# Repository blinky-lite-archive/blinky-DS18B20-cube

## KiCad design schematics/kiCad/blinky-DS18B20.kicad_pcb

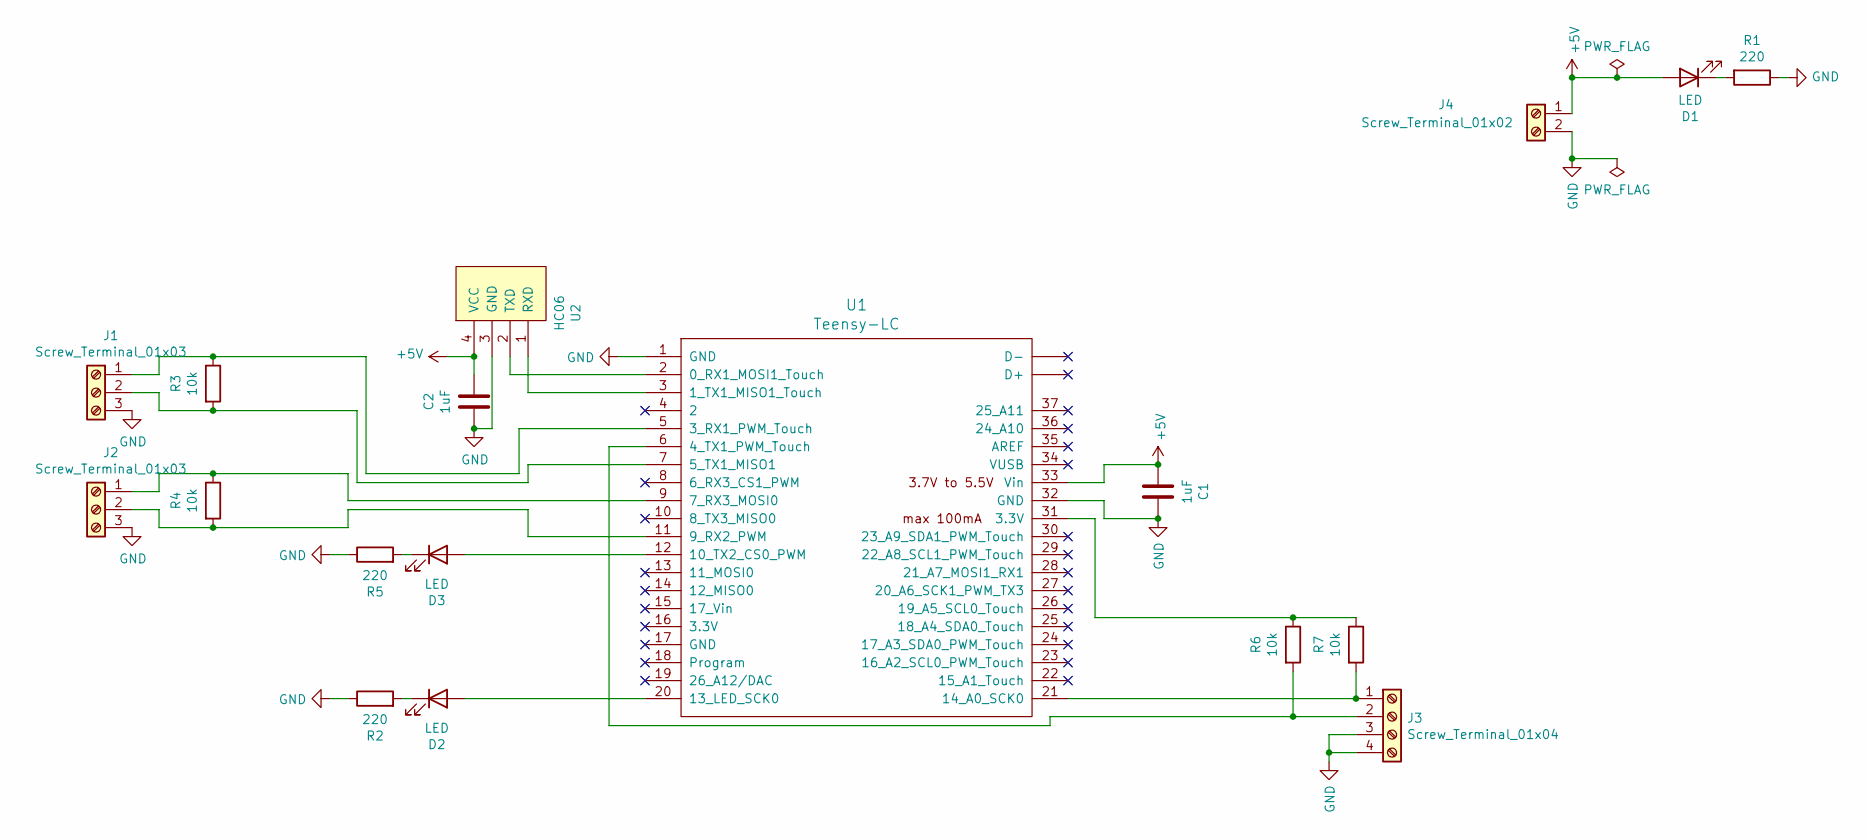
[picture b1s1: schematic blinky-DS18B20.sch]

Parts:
C1, C2: 1uF; C_1206_3216Metric_Pad1.33x1.80mm_HandSolder
D1, D2, D3: LED; LED_D5.0mm
J1, J2: Screw_Terminal_01x03; TerminalBlock_bornier-3_P5.08mm
J3: Screw_Terminal_01x04; TerminalBlock_bornier-4_P5.08mm
J4: Screw_Terminal_01x02; TerminalBlock_bornier-2_P5.08mm
R1, R2, R5: 220; R_1206_3216Metric_Pad1.30x1.75mm_HandSolder
R3, R4, R6, R7: 10k; R_1206_3216Metric_Pad1.30x1.75mm_HandSolder
U1: Teensy-LC; Teensy30_31_32_LC
U2: HC06

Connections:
+5V: C1.2, C2.1, D1.2 (A), J4.1, U1.33 (Vin), U2.4 (VCC)
GND: C1.1, C2.2, J1.3, J2.3, J3.3, J3.4, J4.2, R1.1, R2.1, R5.1, U1.1 (GND), U1.32 (GND), U2.3 (GND)
unnamed: D1.1 (K), R1.2
unnamed: D2.1 (K), R2.2
unnamed: D2.2 (A), U1.20 (13_LED_SCK0)
unnamed: D3.1 (K), R5.2
unnamed: D3.2 (A), U1.12 (10_TX2_CS0_PWM)
unnamed: J1.1, R3.1, U1.5 (3_RX1_PWM_Touch)
unnamed: J1.2, R3.2, U1.7 (5_TX1_MISO1)
unnamed: J2.1, R4.1, U1.9 (7_RX3_MOSI0)
unnamed: J2.2, R4.2, U1.11 (9_RX2_PWM)
unnamed: J3.1, R7.2, U1.21 (14_A0_SCK0)
unnamed: J3.2, R6.2, U1.6 (4_TX1_PWM_Touch)
unnamed: R6.1, R7.1, U1.31 (3.3V)
unnamed: U1.2 (0_RX1_MOSI1_Touch), U2.2 (TXD)
unnamed: U1.3 (1_TX1_MISO1_Touch), U2.1 (RXD)

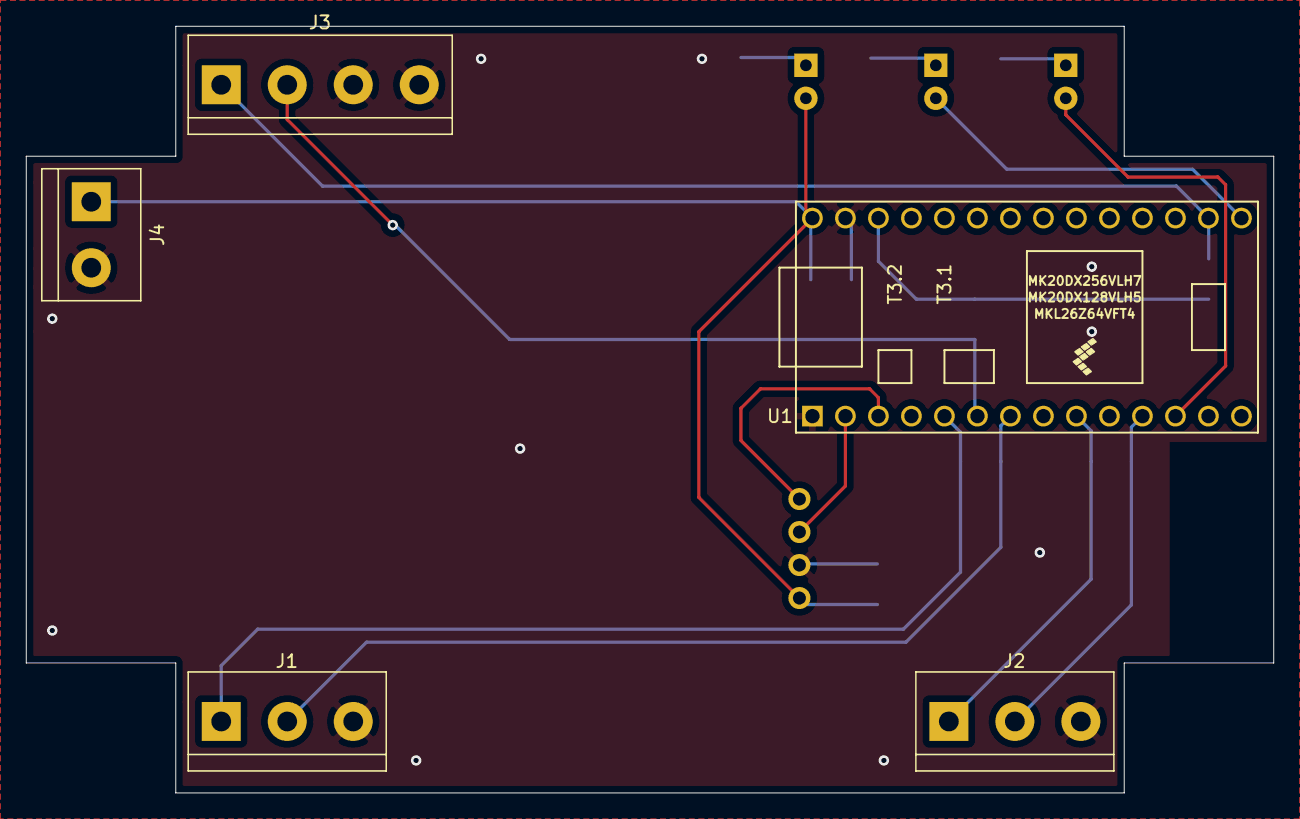
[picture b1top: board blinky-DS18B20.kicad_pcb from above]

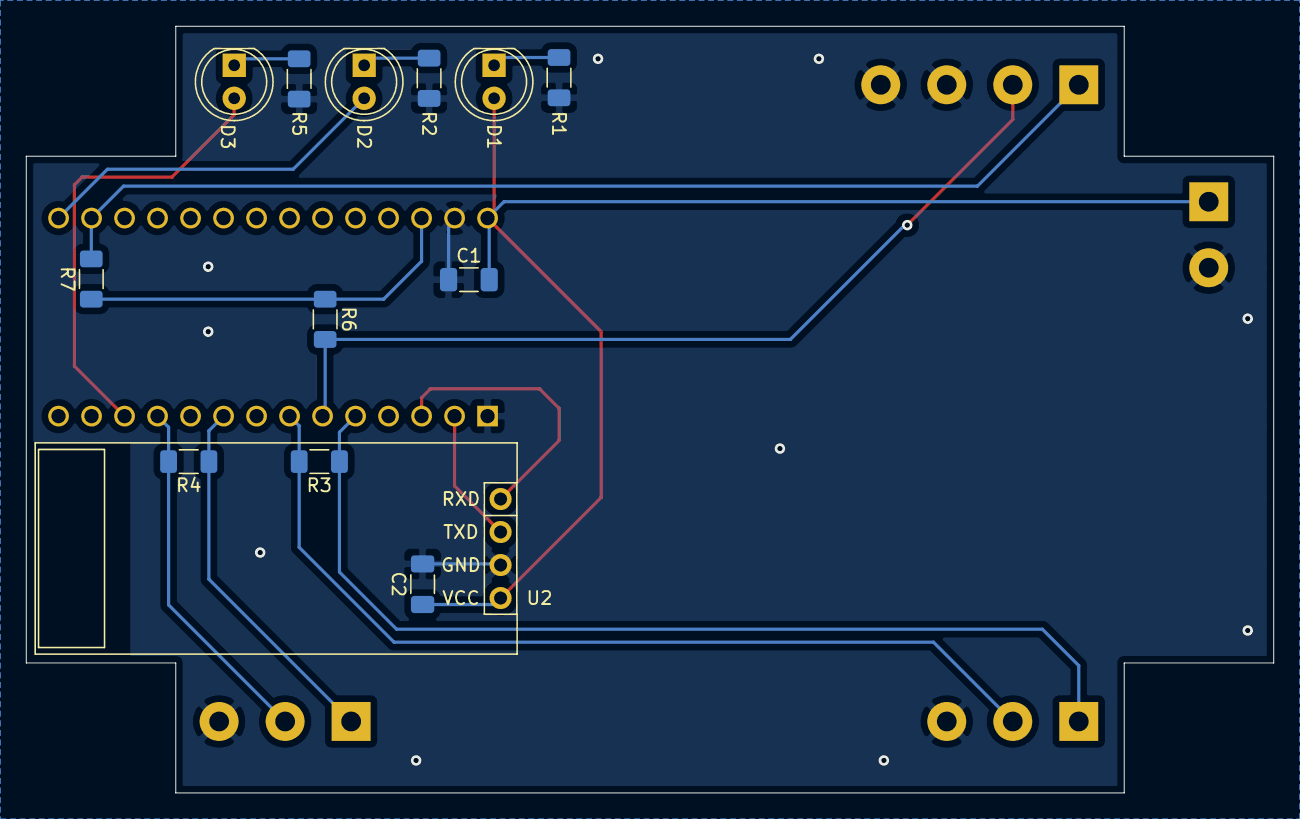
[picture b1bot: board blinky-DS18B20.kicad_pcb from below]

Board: 2 copper layers, 96.0 x 59.0 mm, 18 parts (13 on the bottom side), 16 nets.

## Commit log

2021-05-03 added pcb layout
